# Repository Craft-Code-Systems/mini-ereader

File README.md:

# Mini E-Reader

> A pocket, frontlit e-paper reader you can build and hack.
> ESP32-S3 + 4.26" E-Paper (800×480) + tunable-white frontlight,
> USB-C charged, LiPo powered.

This repository holds the open hardware (KiCad) and project documentation
for a small e-reader. Docs follow the [Colophon](https://usecolophon.dev)
method: a Brief (this file), Decisions (`docs/adr/`), a Log
(`docs/research-log.md`), a Runbook (`docs/runbook.md`), and a Changelog.

> **One KiCad project, one source of truth.** The board lives at the repo root:
> **`ereader.kicad_pcb`**, with the electrical design in the `ereader-*.md`
> docs — `ereader-connection-list.md` (net-by-net source of truth),
> `ereader-schematic.md` (subsystem schematic), `ereader-pcb-design.md`
> (full spec), `ereader-footprints.md` (BOM/footprint picklist) — and the
> `ereader-kicad.net` netlist. (Rev C — placed, planed, stitched, DRC-ruled;
> routing pending.) An earlier, simpler `hardware/` *reference spec* was
> removed once `ereader.*` superseded it; the historical comparison is in
> `docs/research-log.md`. The Rev C parts are reconciled into the ADRs:
> [0006](./docs/adr/0006-i2c-managed-power-path.md) (power) supersedes 0003
> and [0007](./docs/adr/0007-lm3630a-frontlight-driver.md) (frontlight)
> supersedes 0005.

## Why

Commercial e-readers are closed and hard to modify. This is a compact,
documented reference design — cheap parts, two-layer board, hand- or
JLCPCB-assemblable — for reading plain text / EPUB on a persistent,
sunlight-readable display with an adjustable frontlight and Wi-Fi sync.
A buildable learning platform, not a product.

## Scope & non-scope

**In scope**
- Schematic + 2-layer PCB: MCU, 4.26" SPI E-Paper, tunable frontlight,
  power (USB-C + 1S LiPo), buttons, optional microSD.
- A bill of materials and fabrication-ready outputs.
- Automated ERC/DRC + gerber export in CI.

**Out of scope (for now)**
- Enclosure / industrial design (CAD).
- Firmware (tracked separately once hardware is proven).
- Touch input, audio, multi-panel support.
- Certification / mass production.

## Success criteria

1. Schematic captured with **ERC clean** in KiCad 8.
2. PCB placed + routed with **DRC clean**; gerbers export in CI.
3. A built prototype: powers from USB and battery, charges, enumerates
   over native USB, refreshes the E-Paper, and lights the frontlight with
   independent brightness + colour-temperature control.

## Capabilities

- Render text/EPUB to a 4.26" 800×480 monochrome E-Paper panel over SPI.
- Tunable-white frontlight: independent cold/warm channels, PWM brightness
  and colour-temperature mixing.
- Wi-Fi/BLE (ESP32-S3) for fetching and syncing books.
- Battery power (1S LiPo) with USB-C charging and USB-priority power path.
- Battery state-of-charge and charge-status telemetry.
- Three navigation buttons; BOOT/RESET jumper pads (screwdriver-shortable) for flashing.
- Optional microSD for local library storage.

## Non-functional baseline

- **Power:** deep-sleep with the page retained in the µA range; runs from a
  single LiPo; charges over USB-C.
- **Cost/build:** two-layer FR-4, common parts, low-cost assembly.
- **Serviceability:** test points on key rails and buses; native-USB
  programming with no external bridge.
- **Docs:** every significant decision captured as an ADR before it is
  built.

## Stack

- **MCU:** ESP32-S3-WROOM-1 (Wi-Fi/BLE, PSRAM, native USB).
- **Display:** Good Display **GDEY0426T82-FL01C** — 4.26" 800×480 E-Paper,
  controller **SSD1677**, 4-wire SPI, 24-pin FPC, with an integrated dual
  frontlight (5+5 series white LEDs, VF≤15 V, IF≤15 mA).
- **Power:** MCP73831 charger, discrete USB-priority load-share,
  AP2112K-3.3 LDO; 2× TPS61165 frontlight boost drivers.
- **EDA:** KiCad 8. **CI:** GitHub Actions (`kicad-cli` ERC/DRC/export).

## Status & milestones

**v0.1 — design captured; reviewable schematic in `ereader-schematic.md`; native Eeschema `.kicad_sch` + routed PCB not yet drawn in KiCad.**

- [x] Architecture, power tree, net list, pin map — `ereader-pcb-design.md` + `ereader-connection-list.md`
- [x] Decisions recorded — `docs/adr/0001`–`0005`
- [x] KiCad board `ereader.*` placed + config that opens cleanly
- [x] BOM + SKiDL netlist generator
- [x] CI: `kicad-cli` ERC/DRC/export workflow
- [~] Schematic — reviewable subsystem diagrams in `ereader-schematic.md`; native Eeschema capture + **ERC clean** pending
- [ ] PCB placed, routed + **DRC clean**
- [ ] Prototype built + brought up

Live verification state: the milestone checklist above.

Generated overview of these docs (status, Decisions, Changelog, doc freshness): <https://craft-code-systems.github.io/mini-ereader/>

## Key decisions

| # | Decision |
|---|----------|
| [0001](./docs/adr/0001-mcu-esp32-s3.md) | ESP32-S3-WROOM-1 as the MCU |
| [0002](./docs/adr/0002-display-and-frontlight.md) | 4.26" 800×480 E-Paper + laminated tunable frontlight |
| [0003](./docs/adr/0003-power-architecture.md) | USB-C + 1S LiPo, load-share, 3.3 V LDO *(superseded by 0006)* |
| [0004](./docs/adr/0004-native-usb-programming.md) | Native-USB programming (no UART bridge) |
| [0005](./docs/adr/0005-frontlight-driver.md) | Dual boost constant-current frontlight driver *(superseded by 0007)* |
| [0006](./docs/adr/0006-i2c-managed-power-path.md) | I2C-managed power path: BQ25628E + TPS62840 + MAX17048 |
| [0007](./docs/adr/0007-lm3630a-frontlight-driver.md) | LM3630A single-boost dual-sink frontlight driver |
| [0008](./docs/adr/0008-navigation-input.md) | Navigation input: 3 side buttons + ALPS SLLB510200 lever switch |

## Getting started

```
# Open the board in KiCad 8
kicad ereader.kicad_pro

# Read the electrical design (source of truth)
less ereader-connection-list.md
```

See [`docs/runbook.md`](./docs/runbook.md) for capture, verification,
CI, fabrication, and bring-up. Component-level detail lives in
[`ereader-pcb-design.md`](./ereader-pcb-design.md) and
[`ereader-schematic.md`](./ereader-schematic.md).

## Repository layout

```
README.md              This Brief
CHANGELOG.md           Project history
ereader.*              The KiCad board (project, PCB, netlist, cmp)
ereader-*.md           Electrical source of truth: connection-list, schematic, pcb-design, footprints, README
ereader.pretty/        Project footprints (side tactile, ALPS SLLB5 lever)
ereader.3dshapes/      Simple 3D bodies for the project footprints
fp-lib-table           Registers the ereader.pretty footprint library
fab.py                 Gerber/drill export helper (preflight-gated)
gen_netlist.py         SKiDL netlist generator (real symbols → clean import)
preflight.py           Board↔netlist parity check (CI gate; fab.py guard)
docs/
  adr/                 Decisions (0001–0008 + template)
  research-log.md      Dated exploration notes
  runbook.md           Capture / verify / fabricate / bring-up
templates/             Colophon document templates (for ongoing use)
.github/workflows/     CI (KiCad ERC/DRC/export)
```

## License

[MIT](./LICENSE) for code, hardware, and documentation. *(This repository
started from the [Colophon](https://usecolophon.dev) template; the doc
method is reused under MIT here — the template's separate CC BY methodology
license has been removed.)*

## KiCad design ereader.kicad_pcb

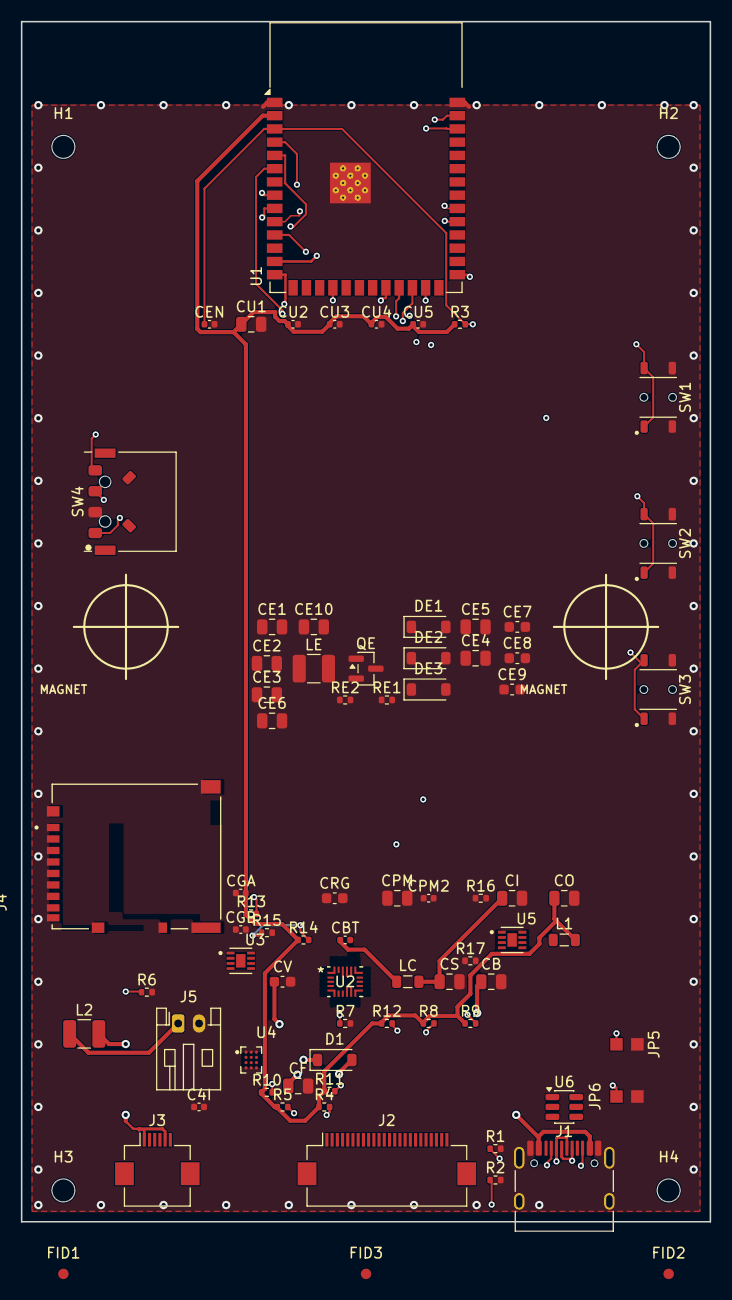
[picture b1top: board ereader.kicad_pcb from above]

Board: 4 copper layers, 66.0 x 115.0 mm, 81 parts (0 on the bottom side), 59 nets.

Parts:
C4I: 1uF; C_0402_1005Metric
CB: 10uF; C_0805_2012Metric
CBT: 47nF; C_0402_1005Metric
CE1, CE2, CE3, CE4, CE5, CE6, CE10: 4.7uF/25V; C_0805_2012Metric
CE7, CE8, CE9: 1uF/25V; C_0603_1608Metric
CEN: 1uF; C_0402_1005Metric
CF: 2.2uF/25V; C_0805_2012Metric
CGA: 0.1uF; C_0402_1005Metric
CGB: 1uF; C_0402_1005Metric
CI: 10uF; C_0805_2012Metric
CO: 10uF; C_0805_2012Metric
CPM: 10uF; C_0805_2012Metric
CPM2: 0.1uF; C_0402_1005Metric
CRG: 4.7uF; C_0603_1608Metric
CS: 10uF; C_0805_2012Metric
CU1: 22uF; C_0805_2012Metric
CU2, CU3, CU4, CU5: 0.1uF; C_0402_1005Metric
CV: 1uF; C_0603_1608Metric
D1: Schottky_30V; D_SOD-123
DE1, DE2, DE3: MBR0530; D_SOD-123
FID1, FID2, FID3: FID; Fiducial_1mm_Mask2mm
H1, H2, H3, H4: M2; MountingHole_2.2mm_M2
J1: USB-C-16P; USB_C_Receptacle_HRO_TYPE-C-31-M-12
J2: EPD_FPC_24P; Hirose_FH12-24S-0.5SH_1x24-1MP_P0.50mm_Horizontal
J3: FL_FPC_6P; Hirose_FH12-6S-0.5SH_1x06-1MP_P0.50mm_Horizontal
J4: microSD; HRS_DM3AT-SF-PEJM5
J5: Battery_1S; JST_PH_S2B-PH-K_1x02_P2.00mm_Horizontal
JP5: BOOT; JumperPad_2P_P2.0mm
JP6: RESET; JumperPad_2P_P2.0mm
L1: 2.2uH; L_0805_2012Metric
L2: 22uH; L_1210_3225Metric
LC: 1uH; L_0805_2012Metric
LE: 47uH; L_1210_3225Metric
QE: Si1308EDL; SOT-23
R1, R2: 5.1k; R_0402_1005Metric
R3, R4, R5, R6, R7: 100k; R_0402_1005Metric
R8, R9, R10, R11: 4.7k; R_0402_1005Metric
R12, R13, R14, R15: 10k; R_0402_1005Metric
R16: 267k; R_0402_1005Metric
R17: 1.65k; R_0402_1005Metric
RE1: 2.2R; R_0402_1005Metric
RE2: 1M; R_0402_1005Metric
SW1: BTN_A; WE_WS-TASU_436351045816
SW2: BTN_B; WE_WS-TASU_436351045816
SW3: BTN_C; WE_WS-TASU_436351045816
SW4: SLLB510200; ALPS_SLLB5_Lever
U1: ESP32-S3-WROOM-1-N16R8; ESP32-S3-WROOM-1
U2: BQ25628E; WQFN-HR18__RYK_TEX
U3: MAX17048; SON50P200X200X80-9N
U4: LM3630A; BGA12N50P4X3_196X146X62
U5: TPS62840; SON50P200X200X80-9N
U6: USBLC6-2SC6; SOT-23-6

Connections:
+3V3: CE6.1, CE7.1, CO.1, CU1.1, CU2.1, CU3.1, CU4.1, CU5.1, J2.15, J2.16, J4.4, L1.2, LE.1, R3.1, R4.1, R5.1, R8.1, R9.1, R10.1, R11.1, R12.1, R13.1, U1.2, U5.8
+SYS: CI.1, CS.1, LC.2, U2.9, U5.2, U5.4
+VBAT: C4I.1, CB.1, CGA.1, CGB.1, J5.1, L2.1, U2.8, U3.2, U3.3, U4.C3
+VBUS: CV.1, J1.A4, J1.A9, J1.B4, J1.B9, U2.18, U6.5
BTN_A: SW1.1, U1.4
BTN_B: SW2.1, U1.5
BTN_C: SW3.1, U1.6
BUCK_SW: L1.1, U5.7
CC1: J1.A5, R1.1
CC2: J1.B5, R2.1
CHG_BTST: CBT.2, U2.1
CHG_CE: R7.1, U1.22, U2.14
CHG_INT: R12.2, U1.24, U2.11
CHG_SW: CBT.1, LC.1, U2.16
EN: CEN.1, JP6.1, R3.2, U1.3
EPD_BUSY: J2.9, U1.7
EPD_CS: J2.12, R4.2, U1.18
EPD_DC: J2.11, U1.17
EPD_GDR: J2.2, QE.1, RE2.1
EPD_MOSI: J2.14, U1.19
EPD_NODEX: CE10.2, DE1.1, DE2.2
EPD_RESE: J2.3, QE.2, RE1.1
EPD_RST: J2.10, U1.12
EPD_SCLK: J2.13, U1.20
EPD_SW: CE10.1, DE3.2, LE.2, QE.3
EPD_VCOM: CE9.1, J2.24
EPD_VDD: CE8.1, J2.18
EPD_VGH: CE5.1, DE3.1, J2.21
EPD_VGL: CE4.1, DE1.2, J2.23
EPD_VSH1: CE1.1, J2.20
EPD_VSH2: CE2.1, J2.5
EPD_VSL: CE3.1, J2.22
FL_COOL_K: J3.2, U4.D3
FL_HWEN: R6.1, U1.23, U4.B1
FL_OUT: CF.1, D1.1, J3.1, J3.5, U4.D1
FL_SW: D1.2, L2.2, U4.A3
FL_WARM_K: J3.6, U4.D2
GAUGE_ALRT: R13.2, U1.25, U3.5
GND: C4I.2, CB.2, CE1.2, CE2.2, CE3.2, CE4.2, CE5.2, CE6.2, CE7.2, CE8.2, CE9.2, CEN.2, CF.2, CGA.2, CGB.2, CI.2, CO.2, CPM.2, CPM2.2, CRG.2, CS.2, CU1.2, CU2.2, CU3.2, CU4.2, CU5.2, CV.2, DE2.1, J1.A1, J1.A12, J1.B1, J1.B12, J1.SH, J2.8, J2.17, J4.6, J4.P1, J4.P2, J4.P3, J4.P4, J5.2, JP5.2, JP6.2, R1.2, R2.2, R6.2, R7.2, R15.2, R16.2, R17.2, RE1.2, RE2.2, SW1.2, SW2.2, SW3.2, SW4.COM, U1.1, U1.40, U1.41, U2.15, U3.1, U3.4, U3.6, U3.9, U4.B3, U4.C1, U4.C2, U5.1, U5.3, U5.6, U5.9, U6.2
I2C0_SCL: R9.2, U1.11, U2.13, U3.7
I2C0_SDA: R8.2, U1.10, U2.12, U3.8
I2C1_SCL: R11.2, U1.31, U4.A2
I2C1_SDA: R10.2, U1.9, U4.A1
ILIM: R17.1, U2.4
IO0_BOOT: JP5.1, U1.27
LEV_CCW: SW4.CCW, U1.38
LEV_CW: SW4.CW, U1.39
LEV_PUSH: SW4.PUSH, U1.8
PMID: CPM.1, CPM2.1, U2.17
REGN: CRG.1, U2.2
SD_CS: J4.2, R5.2, U1.32
SD_MISO: J4.7, U1.33
SD_MOSI: J4.3, U1.35
SD_SCK: J4.5, U1.34
TS: R14.2, R15.1, U2.6
TS_BIAS: R14.1, U2.5
USB_DM: J1.A7, J1.B7, U1.13, U6.3, U6.4
USB_DP: J1.A6, J1.B6, U1.14, U6.1, U6.6
VSET: R16.1, U5.5

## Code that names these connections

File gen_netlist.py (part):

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    # resolver prefix-matches whatever suffix SnapEDA used. Footprints prefer a
    # matching .kicad_mod in ereader.pretty/ (auto), falling back to the string
    # here. ref : (symbol lib_id, fallback footprint)
    "U2": ("ereader:BQ25628E",  "ereader:WQFN-HR18__RYK_TEX"),  # BQ25628E (Ultra Librarian). pins used: VBUS SYS BAT GND SDA SCL *INT(11) *CE(14) TS TS_BIAS REGN PMID SW BTST. RYK HotRod WQFN-HR18: footprint is pads 1-18, NO exposed pad -> nothing to tie.
    "U3": ("ereader:MAX17048",  "ereader:SON50P200X200X80-9N"),  # MAX17048G+T10 = TDFN-8 2x2 WITH EP (pad 9), per the symbol's own package/footprint pairing. The 8N (2x1.5, no-EP) was wrong -> import error "U3 pad 9 not found". pins: CELL VDD GND SDA SCL ~ALERT(5) + CTG/QSTRT/EP->GND.
    "U4": ("ereader:LM3630A",   "ereader:BGA12N50P4X3_196X146X62"),  # LM3630A DSBGA-12. pins: IN GND SDA SCL HWEN SW ILED1 ILED2 OVP (SEL/PWM->GND).
    "U5": ("ereader:TPS62840",  "ereader:SON50P200X200X80-9N"),  # TPS62840 VSON-HR-8 + thermal pad. pins: VIN SW VOS(8=output) GND EN MODE STOP VSET(5=Rset) EP(9=thermal->GND, added to symbol). No FB pin. (9N footprint has pad 9; symbol's own 8N property is overridden by SKiDL.)
    "J2": ("ereader:EPD_GDEY0426T82_FPC24", "Connector_FFC-FPC:Hirose_FH12-24S-0.5SH_1x24-1MP_P0.50mm_Horizontal"),  # 24 pins named by function AND numbered to the panel FPC datasheet
    "J4": ("ereader:DM3AT", "ereader:HRS_DM3AT-SF-PEJM5"),  # DM3AT-SF-PEJM5 microSD. needs: CLK CMD DAT0 DAT3 VDD VSS
    "SW4": ("ereader:ALPS_SLLB5", "ereader:ALPS_SLLB5_Lever"),        # needs: CW CCW PUSH COM
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Net("CHG_SW").connect(U2["SW"], LC[1], CBT[1])
Net("CHG_BTST").connect(U2["BTST"], CBT[2])
Net("TS").connect(U2["TS"], R14[2], R15[1])
Net("TS_BIAS").connect(U2["TS_BIAS"], R14[1])   # TS divider biased from the regulated TS_BIAS pin, NOT +3V3, so thresholds track the reference
Net("REGN").connect(U2["REGN"], CRG[1])                # BQ25628E internal-LDO output: 4.7uF bypass (datasheet Fig 9-1)
Net("PMID").connect(U2["PMID"], CPM[1], CPM2[1])       # BQ25628E PMID: 10uF + 0.1uF bypass (datasheet Fig 9-1)
Net("ILIM").connect(U2["ILIM"], R17[1])                # BQ25628E input-current limit: RILIM=1.65k -> ~1.5A. REQUIRED: EN_EXTILIM resets to 1 (pin active), so an open ILIM would clamp input current to ~0.
Net("VSET").connect(U5["VSET"], R16[1])         # TPS62840 output-voltage select: R16=267k -> 3.3V (datasheet Table 1)
Net("BUCK_SW").connect(U5["SW"], L1[1])
Net("FL_SW").connect(U4["SW"], L2[2], D1["A"])
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Net("EPD_GDR").connect(J2["GDR"], QE["G"], RE2[1])         # Q1 gate; RE2 = 1M pulldown
Net("EPD_RESE").connect(J2["RESE"], QE["S"], RE1[1])       # Q1 source; RE1 = 2.2R sense
Net("EPD_NODEX").connect(CE10[2], DE2["A"], DE1["K"])      # C3 far plate / D2 anode / D1 cathode (pump node)
Net("EPD_VGH").connect(J2["VGH"], DE3["K"], CE5[1])        # PREVGH(+): D3 cathode + C5 reservoir -> panel VGH (pin 21)
Net("EPD_VGL").connect(J2["VGL"], DE1["A"], CE4[1])        # PREVGL(-): D1 anode + C11 reservoir -> panel VGL (pin 23)
Net("EPD_VSH1").connect(J2["VSH1"], CE1[1])   # C9 reservoir  (panel-internal rail)
Net("EPD_VSH2").connect(J2["VSH2"], CE2[1])   # C2 reservoir
Net("EPD_VSL").connect(J2["VSL"], CE3[1])     # C10 reservoir
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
